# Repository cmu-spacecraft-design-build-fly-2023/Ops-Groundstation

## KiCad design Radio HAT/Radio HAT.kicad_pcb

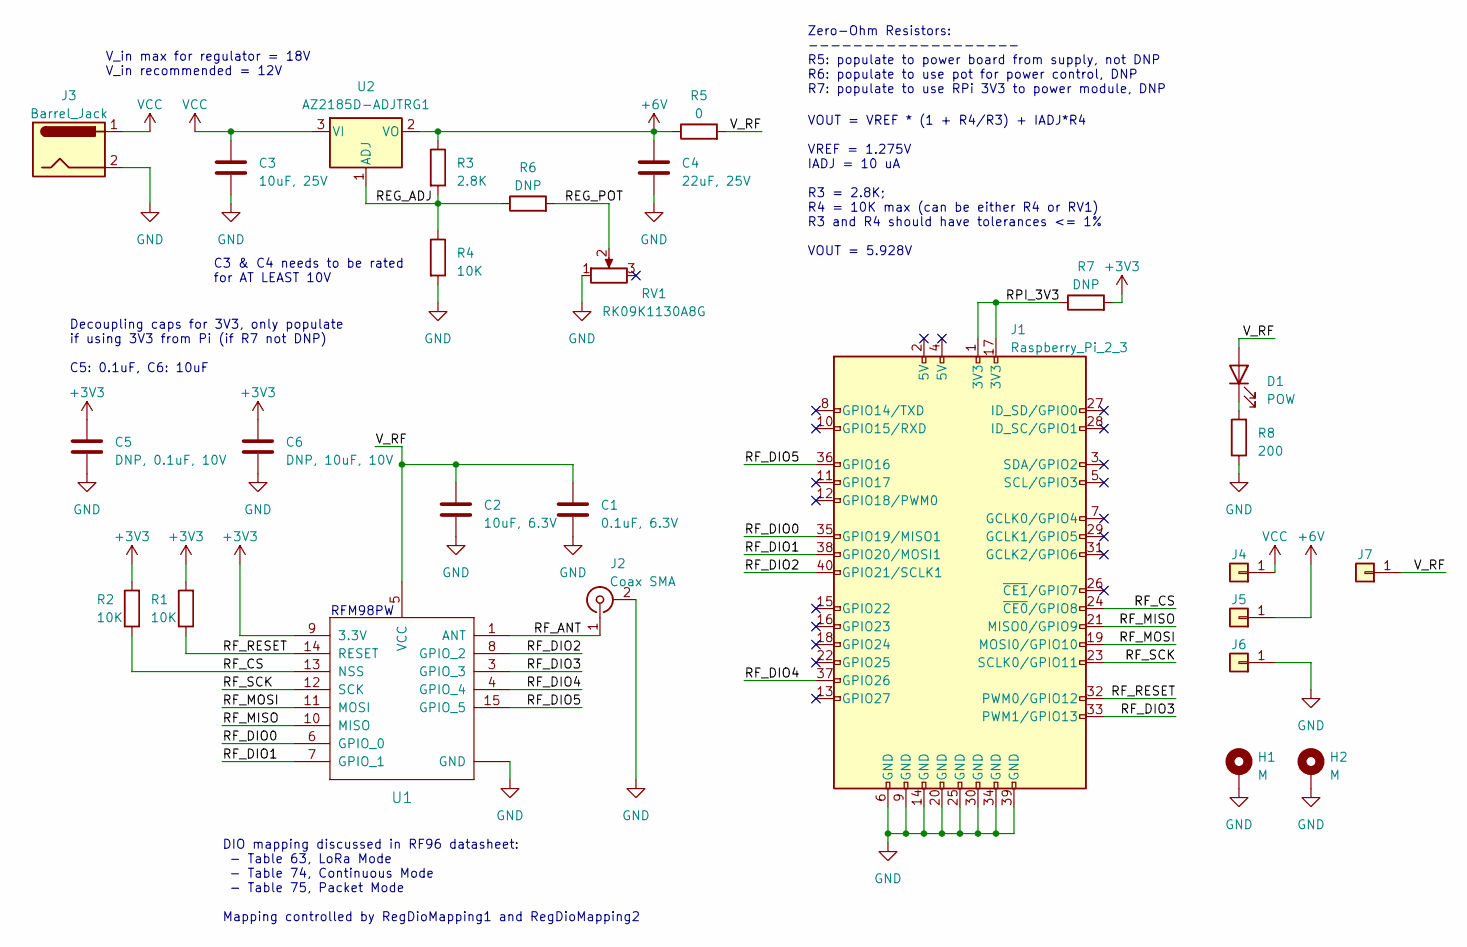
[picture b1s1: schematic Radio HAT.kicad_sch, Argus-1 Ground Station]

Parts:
C1: 0.1uF, 6.3V; C_0603_1608Metric_Pad1.08x0.95mm_HandSolder
C2: 10uF, 6.3V; C_0603_1608Metric_Pad1.08x0.95mm_HandSolder
C3: 10uF, 25V; C_0805_2012Metric_Pad1.18x1.45mm_HandSolder
C4: 22uF, 25V; C_0805_2012Metric_Pad1.18x1.45mm_HandSolder
C5: DNP, 0.1uF, 10V; C_0603_1608Metric_Pad1.08x0.95mm_HandSolder
C6: DNP, 10uF, 10V; C_0603_1608Metric_Pad1.08x0.95mm_HandSolder
D1: POW; LED_0805_2012Metric_Pad1.15x1.40mm_HandSolder
H1, H2: M; MountingHole_2.7mm_M2.5_Pad_Via
J1: Raspberry_Pi_2_3; PinSocket_2x20_P2.54mm_Vertical
J2: Coax SMA; SMA_Amphenol_901-144_Vertical
J3: Barrel_Jack; BarrelJack_Horizontal
J4: VCC; TestPoint_Loop_D2.50mm_Drill1.0mm
J5: 6V; TestPoint_Loop_D2.50mm_Drill1.0mm
J6: GND; TestPoint_Loop_D2.50mm_Drill1.0mm
J7: V_RF; TestPoint_Loop_D2.50mm_Drill1.0mm
R1, R2, R4: 10K; R_0805_2012Metric_Pad1.20x1.40mm_HandSolder
R3: 2.8K; R_0805_2012Metric_Pad1.20x1.40mm_HandSolder
R5: 0; R_1210_3225Metric_Pad1.30x2.65mm_HandSolder
R6, R7: DNP; R_0805_2012Metric_Pad1.20x1.40mm_HandSolder
R8: 200; R_0805_2012Metric_Pad1.20x1.40mm_HandSolder
RV1: RK09K1130A8G; Potentiometer_Alps_RK09K_Single_Vertical
U1: RFM98PW; RFM95PW
U2: AZ2185D-ADJTRG1; TO-252-2

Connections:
+3V3: C5.1, C6.1, R1.2, R2.2, R7.2, U1.9 (3.3V)
+6V: C4.1, J5.1, R3.1, R5.1, U2.2 (VO)
/REG_ADJ: R3.2, R4.1, R6.1, U2.1 (ADJ)
/REG_POT: R6.2, RV1.2
/RF_ANT: J2.1 (In), U1.1 (ANT)
/RF_CS: J1.24 (~CE0/GPIO8), R2.1, U1.13 (NSS)
/RF_DIO0: J1.35 (GPIO19/MISO1), U1.6 (GPIO_0)
/RF_DIO1: J1.38 (GPIO20/MOSI1), U1.7 (GPIO_1)
/RF_DIO2: J1.40 (GPIO21/SCLK1), U1.8 (GPIO_2)
/RF_DIO3: J1.33 (PWM1/GPIO13), U1.3 (GPIO_3)
/RF_DIO4: J1.37 (GPIO26), U1.4 (GPIO_4)
/RF_DIO5: J1.36 (GPIO16), U1.15 (GPIO_5)
/RF_MISO: J1.21 (MISO0/GPIO9), U1.10 (MISO)
/RF_MOSI: J1.19 (MOSI0/GPIO10), U1.11 (MOSI)
/RF_RESET: J1.32 (PWM0/GPIO12), R1.1, U1.14 (RESET)
/RF_SCK: J1.23 (SCLK0/GPIO11), U1.12 (SCK)
/RPI_3V3: J1.1 (3V3), J1.17 (3V3), R7.1
/V_RF: C1.1, C2.1, D1.2 (A), J7.1, R5.2, U1.5 (VCC)
GND: C1.2, C2.2, C3.2, C4.2, C5.2, C6.2, H1.1, H2.1, J1.6 (GND), J1.9 (GND), J1.14 (GND), J1.20 (GND), J1.25 (GND), J1.30 (GND), J1.34 (GND), J1.39 (GND), J2.2 (Ext), J3.2, J6.1, R4.2, R8.1, RV1.1, U1.2 (GND), U1.16 (GND), U1.17 (GND)
unnamed: D1.1 (K), R8.2
VCC: C3.1, J3.1, J4.1, U2.3 (VI)

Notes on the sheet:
Decoupling caps for 3V3, only populate if using 3V3 from Pi (if R7 not DNP) C5: 0.1uF, C6: 10uF
DIO mapping discussed in RF96 datasheet: - Table 63, LoRa Mode - Table 74, Continuous Mode - Table 75, Packet Mode Mapping controlled by RegDioMapping1 and RegDioMapping2
Zero-Ohm Resistors: ------------------- R5: populate to power board from supply, not DNP R6: populate to use pot for power control, DNP R7: populate to use RPi 3V3 to power module, DNP
V_in max for regulator = 18V V_in recommended = 12V
RFM98PW
C3 & C4 needs to be rated for AT LEAST 10V
VOUT = VREF * (1 + R4/R3) + IADJ*R4 VREF = 1.275V IADJ = 10 uA R3 = 2.8K; R4 = 10K max (can be either R4 or RV1) R3 and R4 should have tolerances <= 1% VOUT = 5.928V

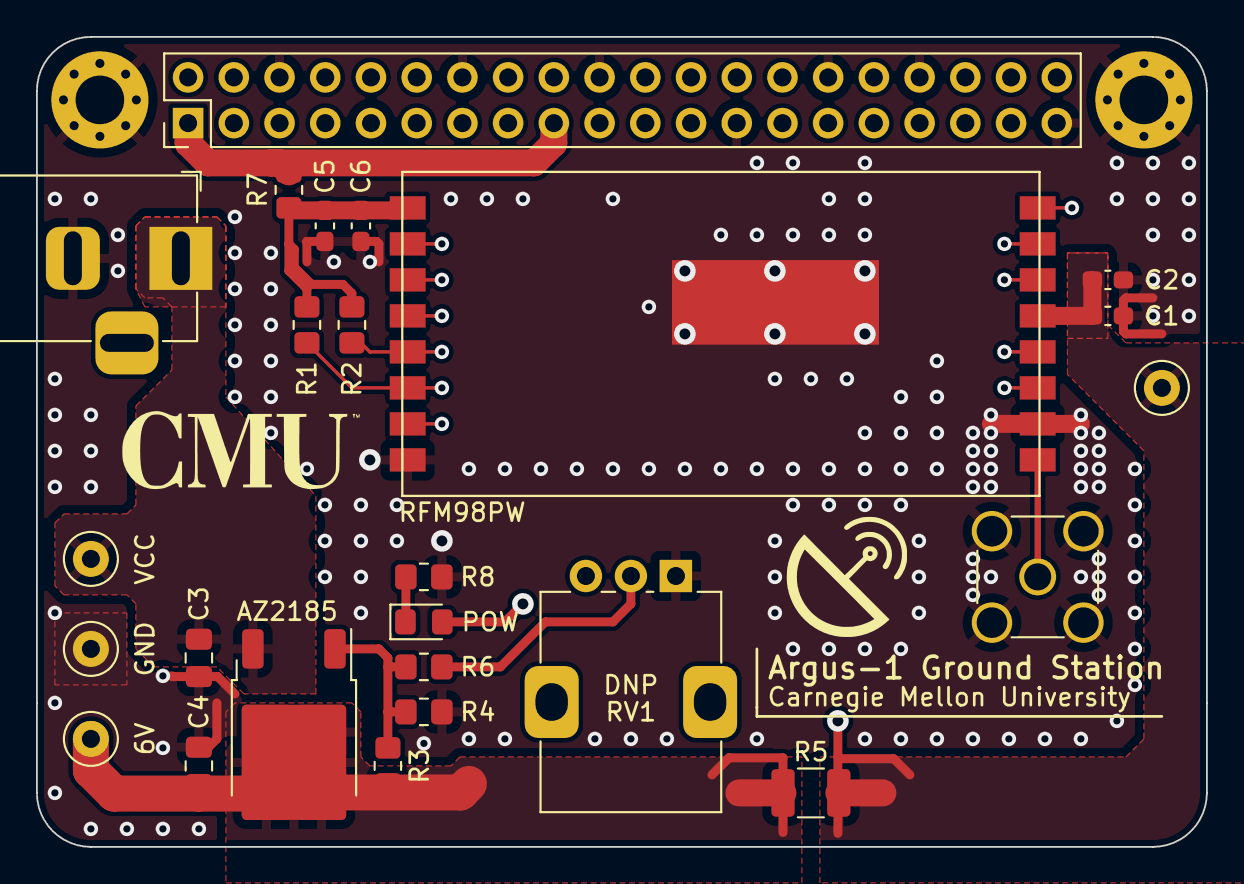
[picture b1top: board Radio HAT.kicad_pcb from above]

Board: 4 copper layers, 65.0 x 45.0 mm, 27 parts (0 on the bottom side), 21 nets.

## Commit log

2023-09-02 Add .gitignore
2023-09-02 Upload files
2023-09-04 Initial schematic design for RFM98 HAT
2023-09-08 Finished schematic, started board layout
2023-09-08 Finished board design
2023-09-10 CubeSat Space Protocol information, as well as calculation tools from AMSAT.
2023-09-10 Implemented changes from PR review
    Changes implemented:
    - added schematic documentation and page settings
    - fixed PCB silkscreen
    - added board rev. and information on back silkscreen
    - added 3D models, generated 3D model for board
    - generated HTML BOM
2023-09-11 Implemented changes from PR
    Fixed 3D models of board, added testpoints on board.
2023-09-11 Reworked GND stitching vias
2023-09-12 v0.0 visualization of GUI with 3D satellite in orbit and mock preloaded data
2023-09-13 Additional communications information.
2023-09-26 Adding initial database implementation.
2023-09-26 More minor updates.
2023-09-26 Adding initial signals, message definitions, and message layouts.
2023-10-02 Added some starter code and helper functions to test packet receiving and transmitting.
2023-10-02 More helpers for packing headers.
2023-10-02 Sending headers from client <> server.
2023-10-09 Add files via upload
    Adding the Semtech datasheet to the References folder.
2023-10-15 Changed connector orientation
    Changed orientation of 40-pin connector, increased board size, added optional pot, added graphics
2023-10-24 Implemented PR feedback by Jason
2023-10-25 Updated schematic, changed power routing
2023-10-27 Inventory Document
2023-10-29 Reworked power traces, added stitching vias
    Reworked 3V3 net, added stitching vias on board, added passive components, regenerated BOM and STEP file for board
2023-10-30 Updated copper pours
    Copper pours had gone out of alignment, reworked and increased sizes
2023-11-01 Converted to 4-layer board
    Changes:
    - added 2 internal layers
    - stackup: PWR - GND - SIG - GND
    - added POW indicator LED
    - increased density of stitching vias
2023-11-07 Changed layer stackup
    Board is now GND-PWR-SIG-GND to shield nets from interference from top and bottom
2023-11-08 Updated via placements
2023-11-10 Radio HAT v1.1 redesign
    Changes:
    - Board is back to PWR-GND-SIG-GND
    - Made small electrical changes in a lot of spots with Jason
2023-11-11 Impedance matched ANT trace
2023-11-20 Added gerbers, fixed silkscreen overlaps
    Minor fixes to fix parts of silkscreen overlapping or crossing into footprints, generated gerber files for v1.1
2024-01-18 Fixed LED placement
    LED was initially placed backwards
2024-02-12 Updated BOM, removed gerbers

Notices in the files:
Radio HAT/Radio HAT.kicad_pcb:
LICENSE: CC BY 4.0
